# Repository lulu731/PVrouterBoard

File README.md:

# PVrouterBoard
PCB to manage PV power routing.

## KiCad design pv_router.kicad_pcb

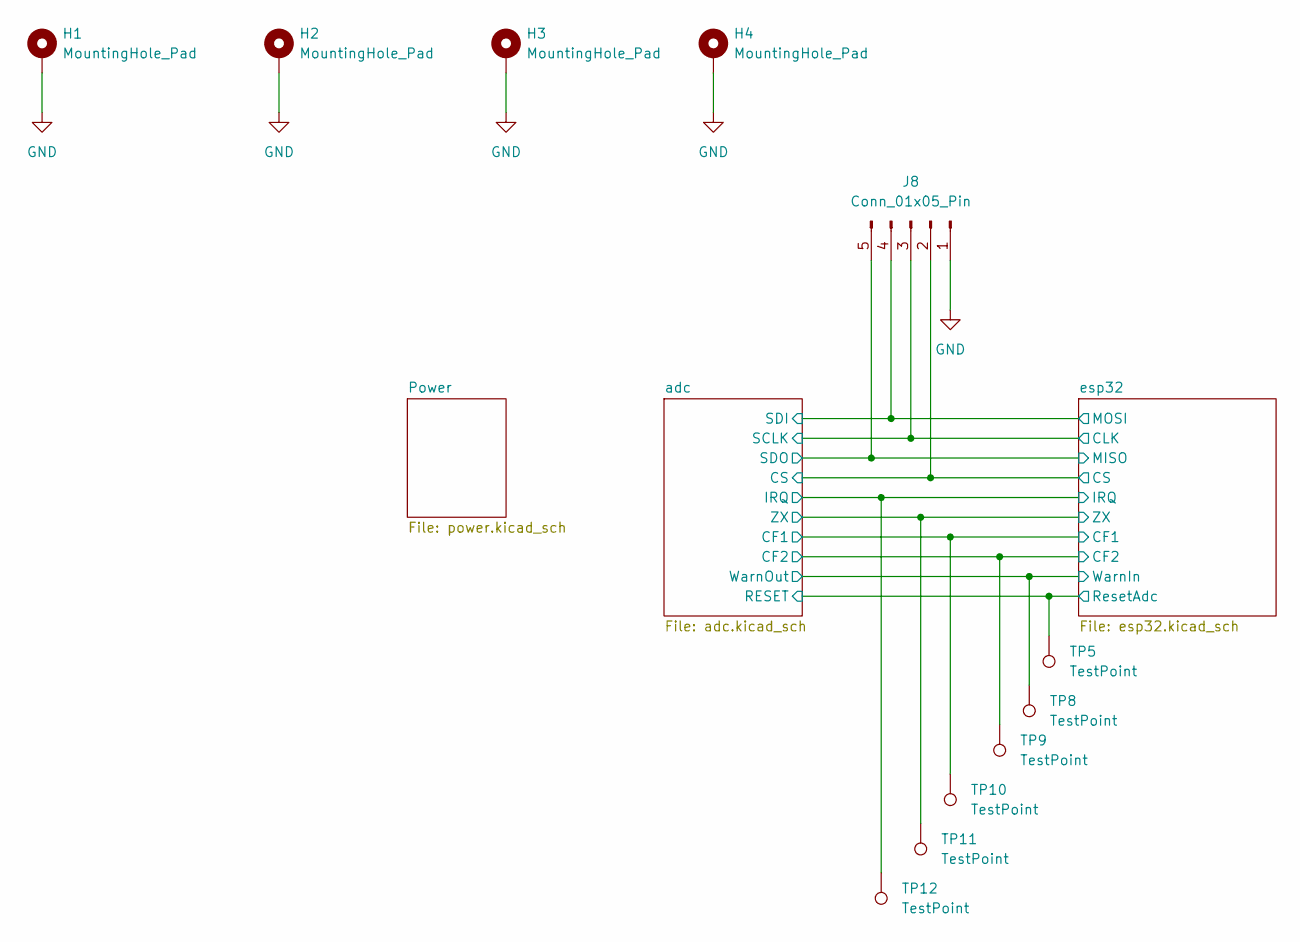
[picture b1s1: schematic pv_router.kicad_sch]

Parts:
H1, H2, H3, H4: MountingHole_Pad; MountingHole_2.7mm_Pad
J8: Conn_01x05_Pin; PinHeader_1x05_P2.54mm_Vertical
TP5, TP8, TP9, TP10, TP11, TP12: TestPoint; TestPoint_Pad_D1.0mm

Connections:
/adc/CF1: TP10.1; also elsewhere on the board
/adc/CF2: TP9.1; also elsewhere on the board
/adc/CS: J8.2; also elsewhere on the board
/adc/IRQ: TP12.1; also elsewhere on the board
/adc/RESET: TP5.1; also elsewhere on the board
/adc/SCLK: J8.3; also elsewhere on the board
/adc/SDI: J8.4; also elsewhere on the board
/adc/SDO: J8.5; also elsewhere on the board
/adc/WarnOut: TP8.1; also elsewhere on the board
/adc/ZX: TP11.1; also elsewhere on the board
GND: H1.1, H2.1, H3.1, H4.1, J8.1; also elsewhere on the board

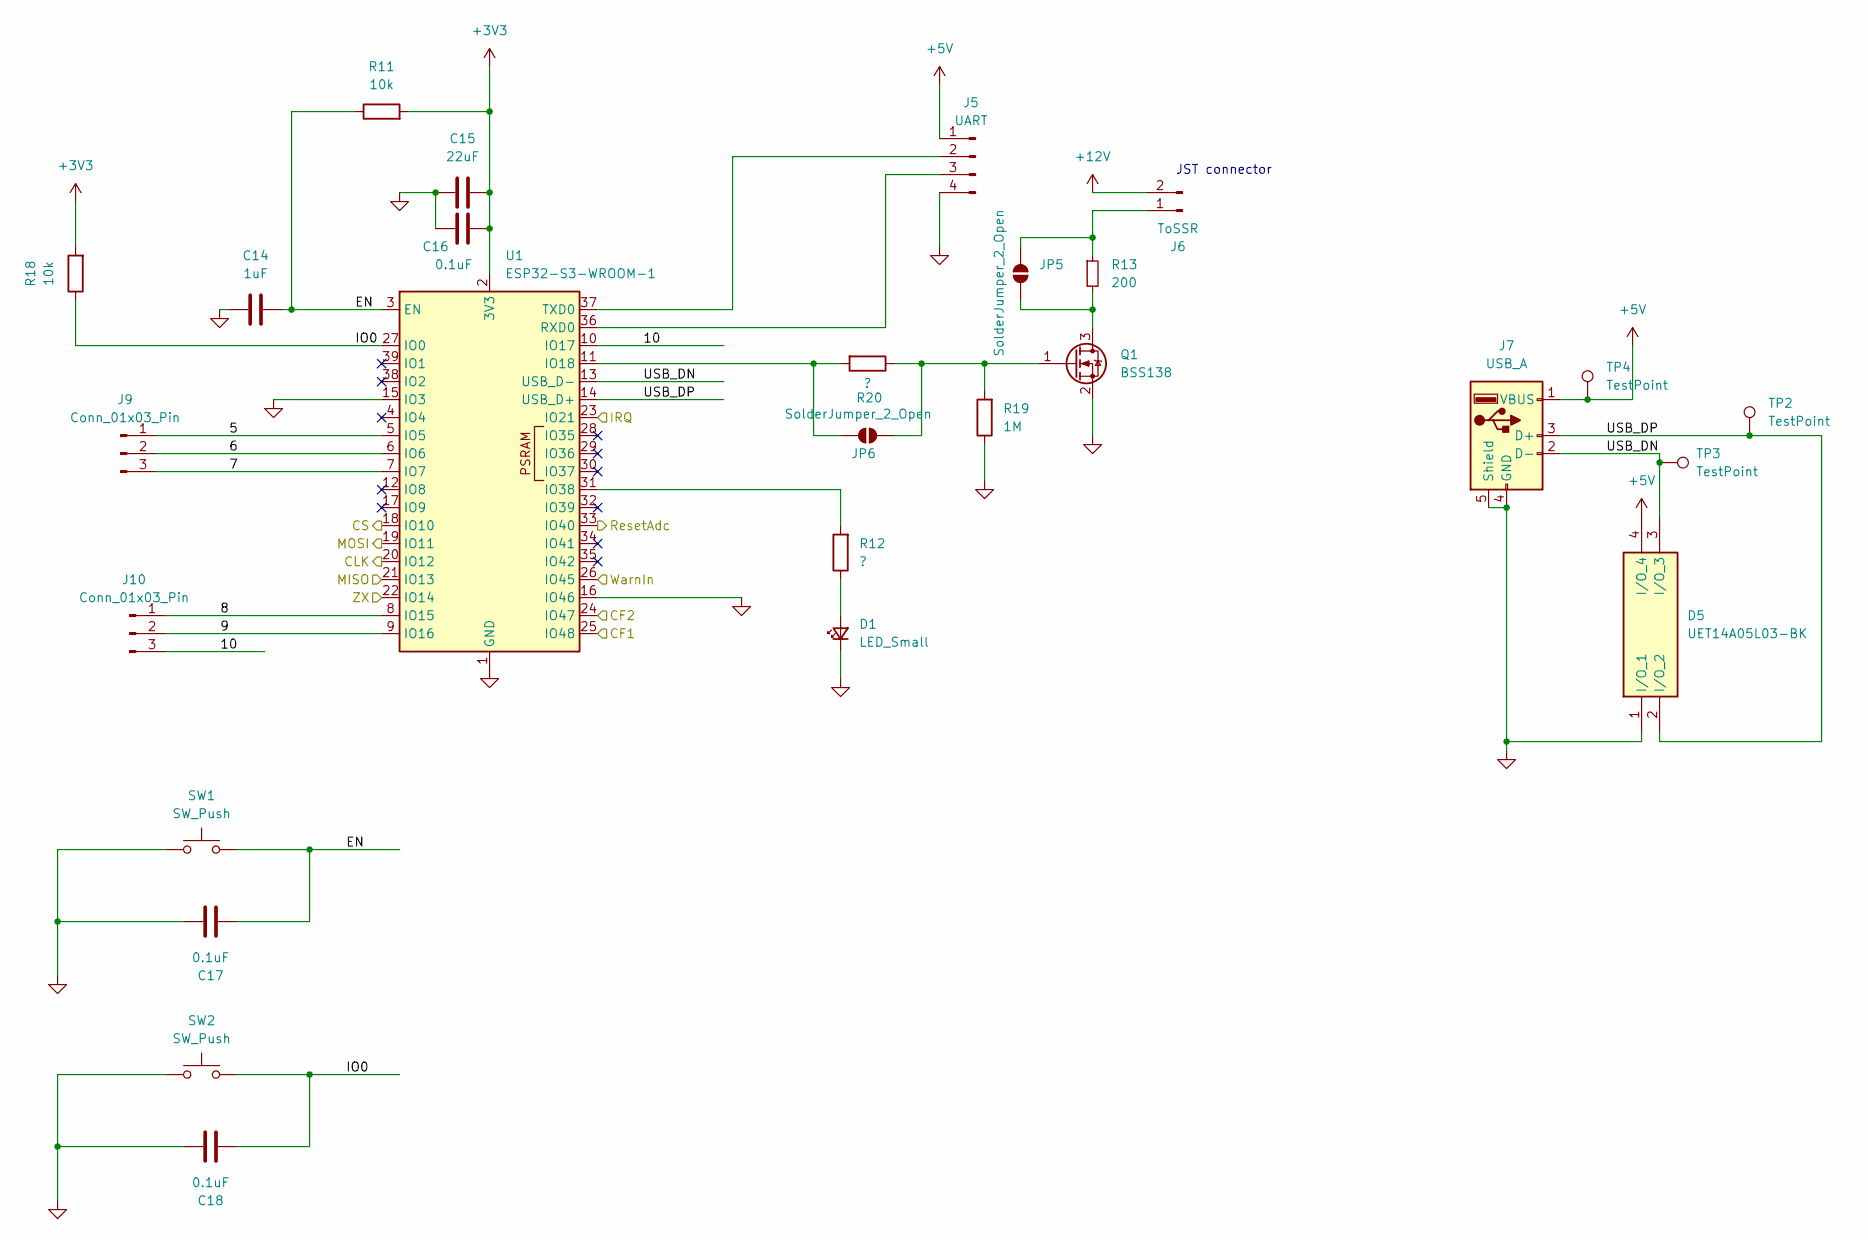
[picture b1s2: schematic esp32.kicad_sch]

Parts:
C14: 1uF; C_0805_2012Metric_Pad1.18x1.45mm_HandSolder
C15: 22uF; C_1210_3225Metric_Pad1.33x2.70mm_HandSolder
C16, C17, C18: 0.1uF; C_0805_2012Metric_Pad1.18x1.45mm_HandSolder
D1: LED_Small; LED_1206_3216Metric_Pad1.42x1.75mm_HandSolder
D5: UET14A05L03-BK; UET14A05L03BK; Mouser Part Number 603-UET14A05L03-BK
J5: UART; PinHeader_1x04_P2.54mm_Vertical
J6: ToSSR; JST_XH_S2B-XH-A_1x02_P2.50mm_Horizontal
J7: USB_A; USB-2.0-TYPE-A
J9, J10: Conn_01x03_Pin; PinHeader_1x03_P2.54mm_Vertical
JP5, JP6: SolderJumper_2_Open; SolderJumper-2_P1.3mm_Open_TrianglePad1.0x1.5mm
Q1: BSS138; SOT-23_Handsoldering
R11, R18: 10k; R_0805_2012Metric_Pad1.20x1.40mm_HandSolder
R12, R20: ?; R_Axial_DIN0207_L6.3mm_D2.5mm_P7.62mm_Horizontal
R13: 200; R_Axial_DIN0207_L6.3mm_D2.5mm_P7.62mm_Horizontal
R19: 1M; R_Axial_DIN0207_L6.3mm_D2.5mm_P7.62mm_Horizontal
SW1, SW2: SW_Push; SW_SPST_EVQQ2
TP2, TP3: TestPoint; TestPoint_THTPad_D1.5mm_Drill0.7mm
TP4: TestPoint; TestPoint_Pad_D2.0mm
U1: ESP32-S3-WROOM-1

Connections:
+3V3: C15.2, C16.2, R11.2, R18.2, U1.2 (3V3); also elsewhere on the board
+5V: D5.4 (I/O), J5.1, J7.1 (VBUS), TP4.1; also elsewhere on the board
+12V: J6.2; also elsewhere on the board
/adc/CF1: U1.25 (IO48); also elsewhere on the board
/adc/CF2: U1.24 (IO47); also elsewhere on the board
/adc/CS: U1.18 (IO10); also elsewhere on the board
/adc/IRQ: U1.23 (IO21); also elsewhere on the board
/adc/RESET: U1.33 (IO40); also elsewhere on the board
/adc/SCLK: U1.20 (IO12); also elsewhere on the board
/adc/SDI: U1.19 (IO11); also elsewhere on the board
/adc/SDO: U1.21 (IO13); also elsewhere on the board
/adc/WarnOut: U1.26 (IO45); also elsewhere on the board
/adc/ZX: U1.22 (IO14); also elsewhere on the board
/esp32/5: J9.1, U1.5 (IO5)
/esp32/6: J9.2, U1.6 (IO6)
/esp32/7: J9.3, U1.7 (IO7)
/esp32/8: J10.1, U1.8 (IO15)
/esp32/9: J10.2, U1.9 (IO16)
/esp32/10: J10.3, U1.10 (IO17)
/esp32/EN: C14.2, C17.2, R11.1, SW1.2, U1.3 (EN)
/esp32/IO0: C18.2, R18.1, SW2.2, U1.27 (IO0)
/esp32/USB_DN: D5.3 (I/O), J7.2 (D-), TP3.1, U1.13 (USB_D-)
/esp32/USB_DP: D5.2 (I/O), J7.3 (D+), TP2.1, U1.14 (USB_D+)
GND: C14.1, C15.1, C16.1, C17.1, C18.1, D1.1 (K), D5.1 (I/O), J5.4, J7.4 (GND), J7.5 (Shield), Q1.2 (S), R19.1, SW1.1, SW2.1, U1.1 (GND), U1.15 (IO3), U1.16 (IO46), U1.40 (GND), U1.41 (GND); also elsewhere on the board
unnamed: D1.2 (A), R12.1
unnamed: J5.2, U1.37 (TXD0)
unnamed: J5.3, U1.36 (RXD0)
unnamed: J6.1, JP5.2 (B), R13.1
unnamed: JP5.1 (A), Q1.3 (D), R13.2
unnamed: JP6.1 (A), R20.2, U1.11 (IO18)
unnamed: JP6.2 (B), Q1.1 (G), R19.2, R20.1
unnamed: R12.2, U1.31 (IO38)

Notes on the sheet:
JST connector

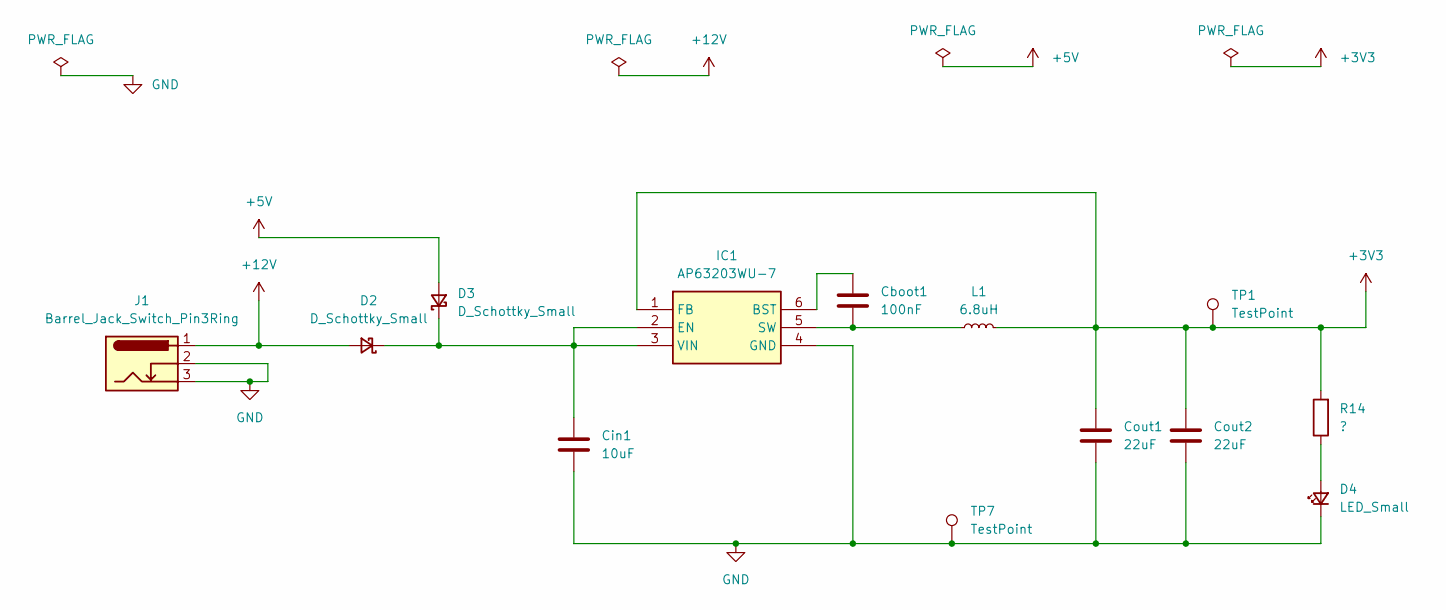
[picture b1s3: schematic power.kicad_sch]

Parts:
Cboot1: 100nF; C_0805_2012Metric_Pad1.18x1.45mm_HandSolder
Cin1: 10uF; C_0805_2012Metric_Pad1.18x1.45mm_HandSolder
Cout1, Cout2: 22uF; C_1210_3225Metric_Pad1.33x2.70mm_HandSolder
D2, D3: D_Schottky_Small; SODFL4724X90N
D4: LED_Small; LED_1206_3216Metric_Pad1.42x1.75mm_HandSolder
IC1: AP63203WU-7; AP63203WU7; Mouser Part Number 621-AP63203WU-7
J1: Barrel_Jack_Switch_Pin3Ring; BarrelJack_CUI_PJ-051A_Horizontal
L1: 6.8uH; L_Bourns_SRR1260
R14: ?; R_Axial_DIN0207_L6.3mm_D2.5mm_P7.62mm_Horizontal
TP1: TestPoint; TestPoint_Pad_D2.0mm
TP7: TestPoint; TestPoint_THTPad_D1.5mm_Drill0.7mm

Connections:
+3V3: Cout1.1, Cout2.1, IC1.1 (FB), L1.2, R14.2, TP1.1; also elsewhere on the board
+5V: D3.2 (A); also elsewhere on the board
+12V: D2.2 (A), J1.1; also elsewhere on the board
GND: Cin1.1, Cout1.2, Cout2.2, D4.1 (K), IC1.4 (GND), J1.2, J1.3, TP7.1; also elsewhere on the board
unnamed: Cin1.2, D2.1 (K), D3.1 (K), IC1.2 (EN), IC1.3 (VIN)
unnamed: D4.2 (A), R14.1
unnamed: Cboot1.2, IC1.6 (BST)
unnamed: Cboot1.1, IC1.5 (SW), L1.1

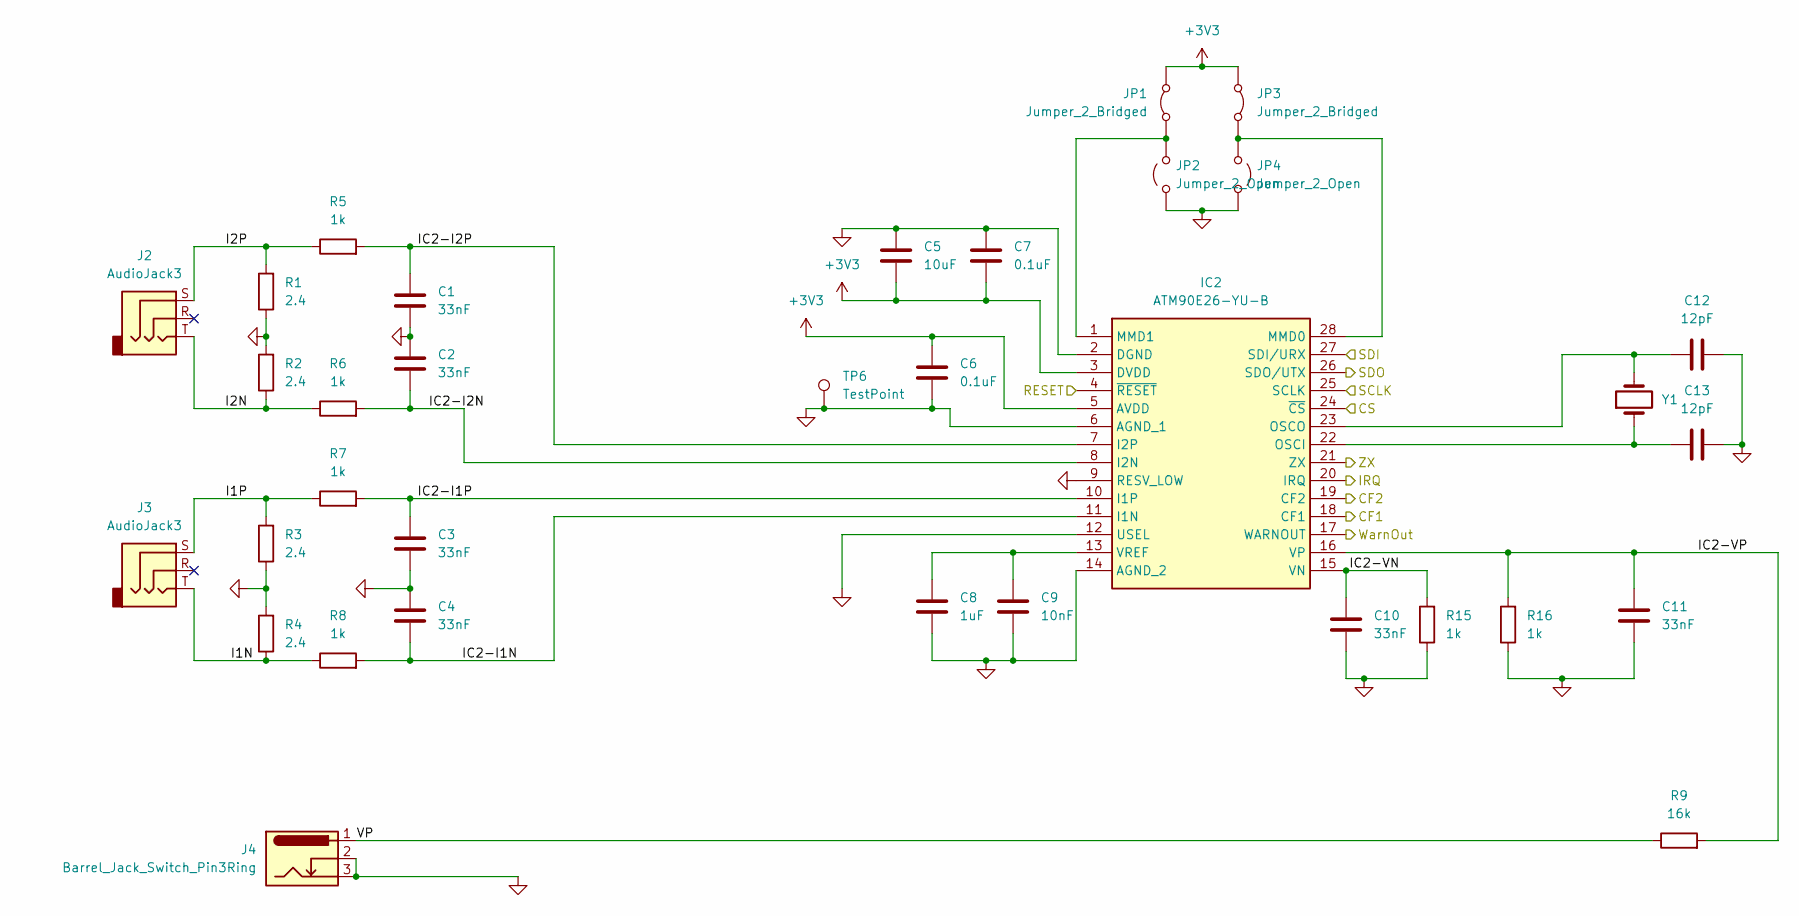
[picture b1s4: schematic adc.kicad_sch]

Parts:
C1, C2, C3, C4, C10, C11: 33nF; C_0805_2012Metric_Pad1.18x1.45mm_HandSolder
C5: 10uF; C_1210_3225Metric_Pad1.33x2.70mm_HandSolder
C6, C7: 0.1uF; C_0805_2012Metric_Pad1.18x1.45mm_HandSolder
C8: 1uF; C_0805_2012Metric_Pad1.18x1.45mm_HandSolder
C9: 10nF; C_0805_2012Metric_Pad1.18x1.45mm_HandSolder
C12, C13: 12pF; C_0805_2012Metric_Pad1.18x1.45mm_HandSolder
IC2: ATM90E26-YU-B; SOP65P778X199-28N; Mouser Part Number 556-ATM90E26-YU-B
J2, J3: AudioJack3; Jack_3.5mm_CUI_SJ1-3523N_Horizontal
J4: Barrel_Jack_Switch_Pin3Ring; BarrelJack_CUI_PJ-051A_Horizontal
JP1, JP3: Jumper_2_Bridged; TestPoint_2Pads_Pitch2.54mm_Drill0.8mm
JP2, JP4: Jumper_2_Open; TestPoint_2Pads_Pitch2.54mm_Drill0.8mm
R1, R2, R3, R4: 2.4; R_0805_2012Metric_Pad1.20x1.40mm_HandSolder
R5, R6, R7, R8, R15, R16: 1k; R_0805_2012Metric_Pad1.20x1.40mm_HandSolder
R9: 16k; R_0805_2012Metric_Pad1.20x1.40mm_HandSolder
TP6: TestPoint; TestPoint_THTPad_D1.5mm_Drill0.7mm
Y1: 8.192Mhz; HC_49US-_AT49__1

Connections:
+3V3: C5.2, C6.1, C7.2, IC2.3 (DVDD), IC2.5 (AVDD), JP1.2 (B), JP3.1 (A); also elsewhere on the board
/adc/CF1: IC2.18 (CF1); also elsewhere on the board
/adc/CF2: IC2.19 (CF2); also elsewhere on the board
/adc/CS: IC2.24 (~CS); also elsewhere on the board
/adc/I1N: J3.T, R4.1, R8.1
/adc/I1P: J3.S, R3.2, R7.1
/adc/I2N: J2.T, R2.1, R6.1
/adc/I2P: J2.S, R1.2, R5.1
/adc/IC2-I1N: C4.2, IC2.11 (I1N), R8.2
/adc/IC2-I1P: C3.1, IC2.10 (I1P), R7.2
/adc/IC2-I2N: C2.2, IC2.8 (I2N), R6.2
/adc/IC2-I2P: C1.1, IC2.7 (I2P), R5.2
/adc/IC2-VN: C10.1, IC2.15 (VN), R15.2
/adc/IC2-VP: C11.1, IC2.16 (VP), R9.2, R16.2
/adc/IRQ: IC2.20 (IRQ); also elsewhere on the board
/adc/RESET: IC2.4 (~RESET); also elsewhere on the board
/adc/SCLK: IC2.25 (SCLK); also elsewhere on the board
/adc/SDI: IC2.27 (SDI/URX); also elsewhere on the board
/adc/SDO: IC2.26 (SDO/UTX); also elsewhere on the board
/adc/VP: J4.1, R9.1
/adc/WarnOut: IC2.17 (WARNOUT); also elsewhere on the board
/adc/ZX: IC2.21 (ZX); also elsewhere on the board
GND: C1.2, C2.1, C3.2, C4.1, C5.1, C6.2, C7.1, C8.2, C9.2, C10.2, C11.2, C12.2, C13.2, IC2.2 (DGND), IC2.6 (AGND_1), IC2.9 (RESV_LOW), IC2.12 (USEL), IC2.14 (AGND_2), J4.2, J4.3, JP2.1 (A), JP4.2 (B), R1.1, R2.2, R3.1, R4.2, R15.1, R16.1, TP6.1; also elsewhere on the board
unnamed: IC2.28 (MMD0), JP3.2 (B), JP4.1 (A)
unnamed: IC2.1 (MMD1), JP1.1 (A), JP2.2 (B)
unnamed: C13.1, IC2.22 (OSCI), Y1.1
unnamed: C12.1, IC2.23 (OSCO), Y1.2
unnamed: C8.1, C9.1, IC2.13 (VREF)

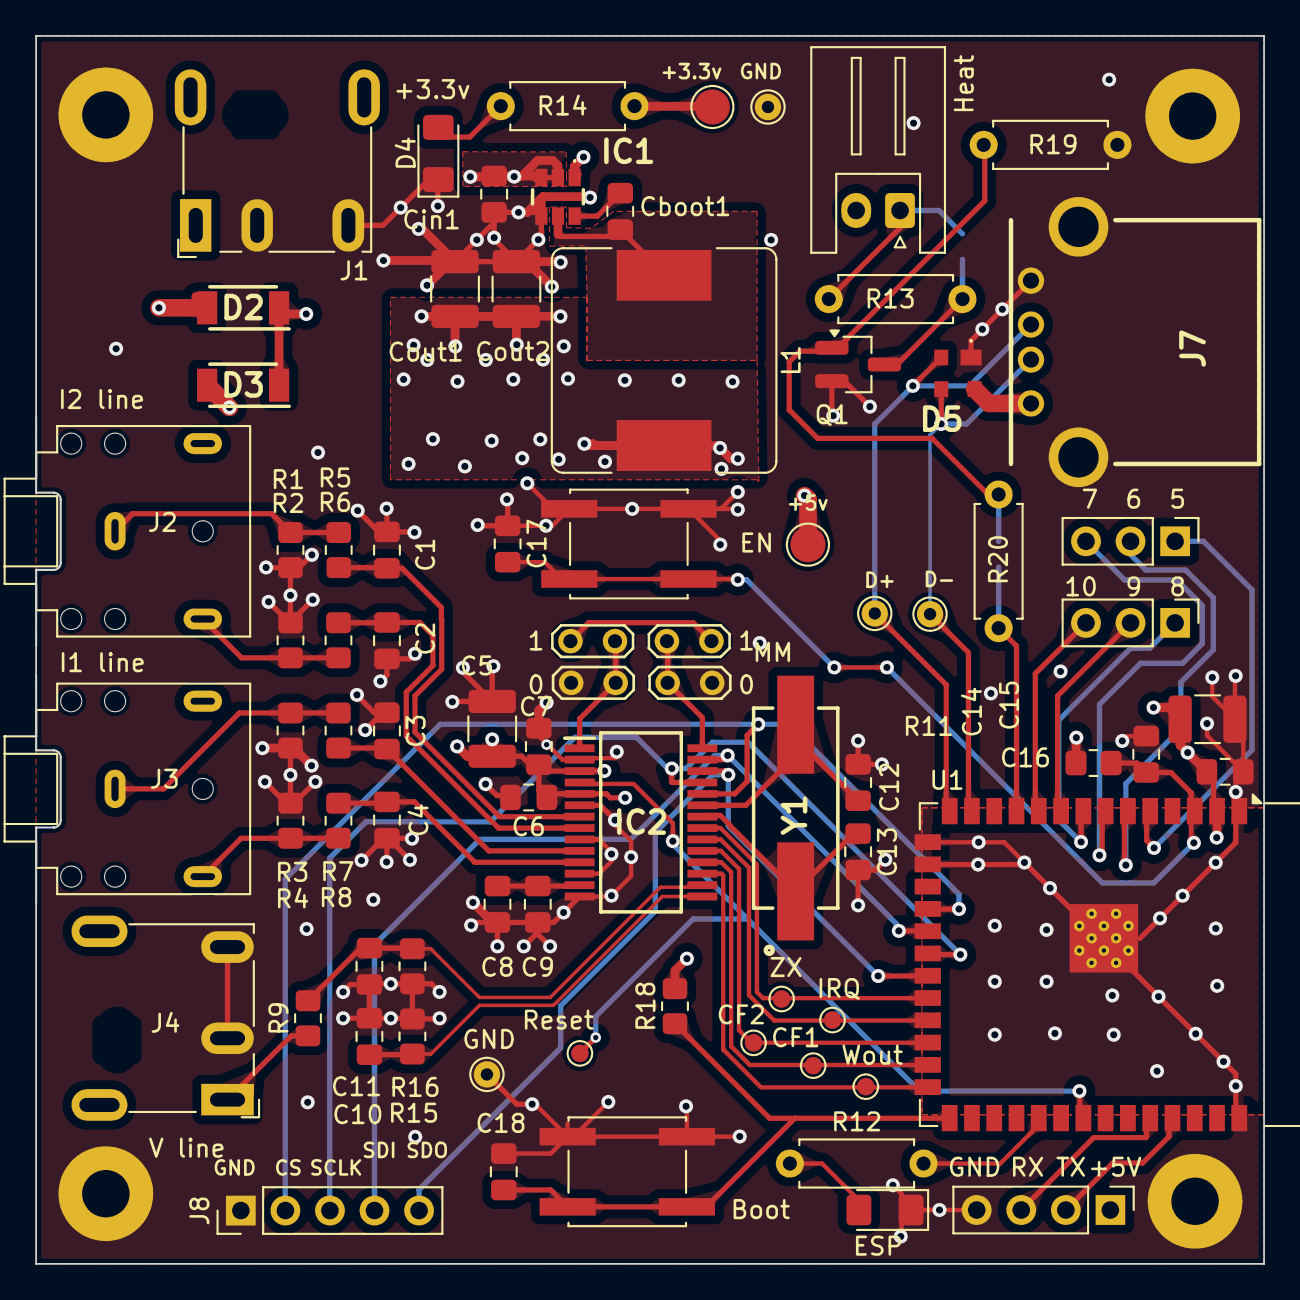
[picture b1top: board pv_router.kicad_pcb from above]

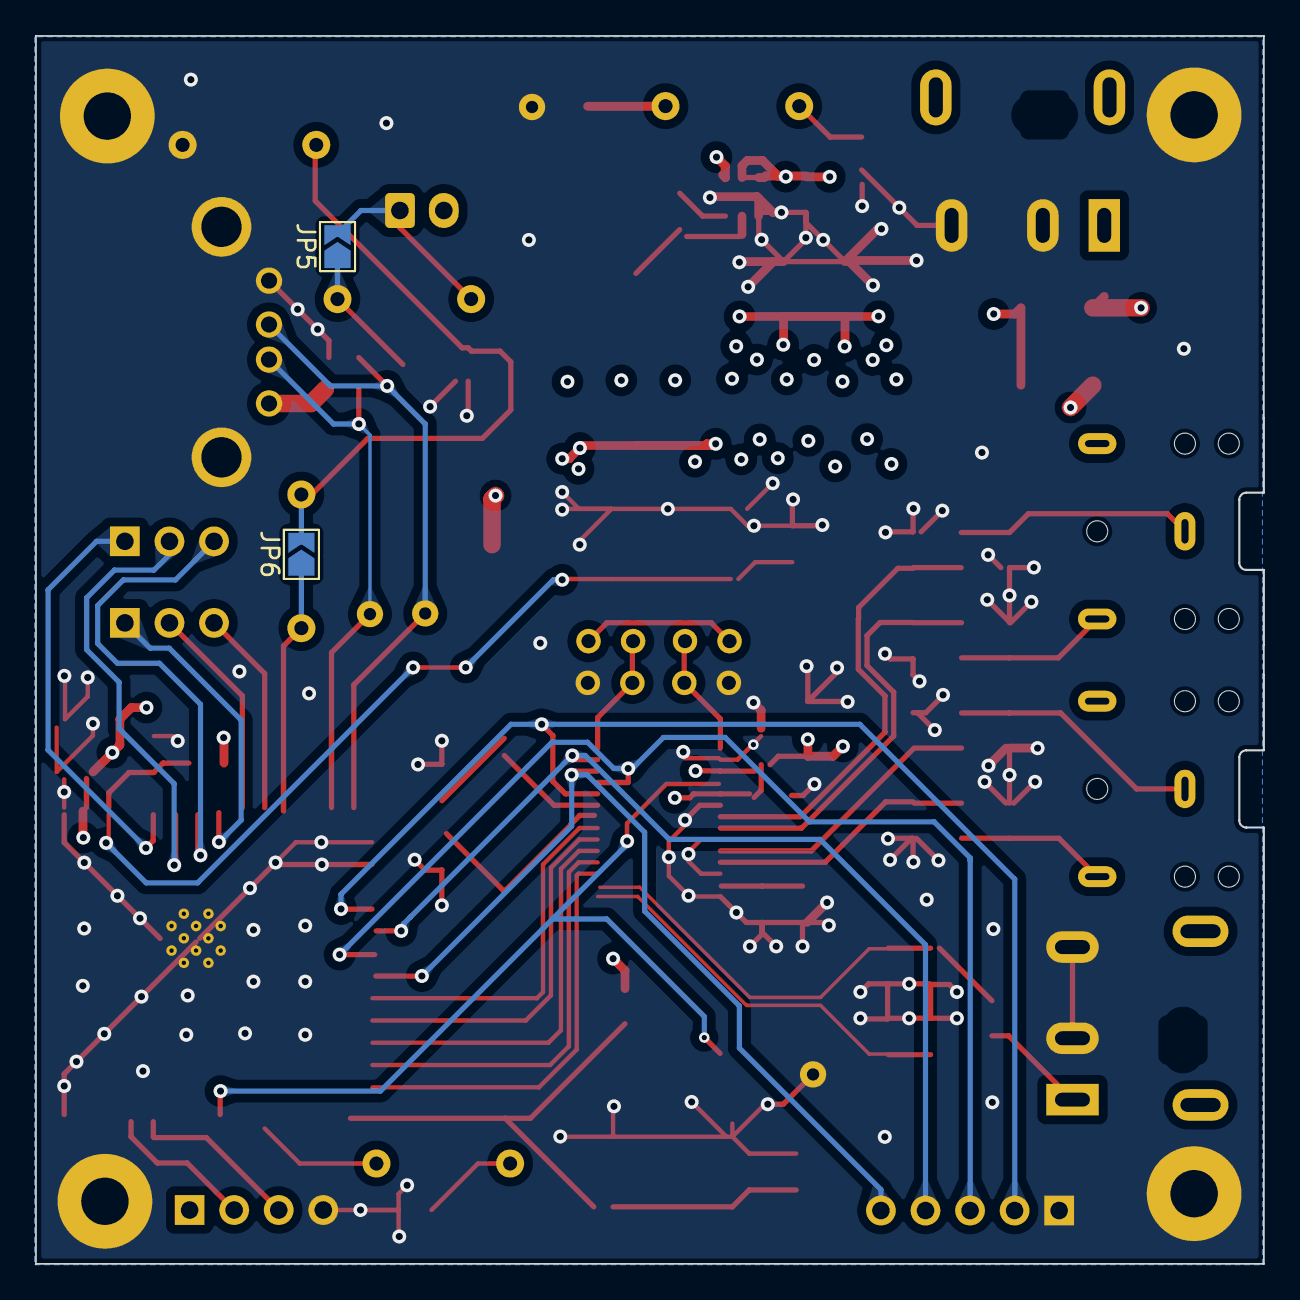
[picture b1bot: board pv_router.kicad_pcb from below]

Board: 4 copper layers, 70.0 x 70.0 mm, 85 parts (2 on the bottom side), 52 nets.

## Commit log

2023-12-12 ci: ignore .lck files and ignore/ dir
2023-12-12 feat: ADC + power 5V and USB
2024-01-04 lib: add ATM M90E26 AFE
2024-01-05 lib: add L6981 3.3V buck converter
2024-01-05 schem: update power sheet with L6981 3.3V buck converter
2024-01-06 feat: add adc component and associated sheet
2024-01-10 fix: anti-aliasing filters and adc grounding
2024-01-11 feat: add esp32 component
2024-01-12 ERC checked
2024-01-19 refactor: add burden resistor on CT lines
2024-01-22 PCB : add barrel jack FP
2024-01-22 fix: connections with sensors (CT and voltage)
2024-01-22 feat: add MOSFET to drive SSR
2024-01-22 check: ERC rules
2024-01-22 FP: assigned
2024-01-22 refactor: replace symbols
2024-01-22 fix: connect pin
2024-01-22 fix: init symbols references
2024-01-23 fix: assigned FP for ICs
2024-01-23 pcb: power module FPs set
2024-01-24 stagged
2024-01-25 fix: delete connection btw SDO and CLK net
2024-01-25 refactor: split 6 resistors network of low band filters in 2 + 4 networks
2024-01-25 pcb: first placement of FP, before routing
2024-01-28 pcb: first routing with freerouting
2024-01-28 ci: ignore *.kicad_pcb.zip files
2024-01-30 pcb: fix inductor value to 33uH
2024-01-30 FP: add inductor lib
2024-01-31 pcb: update stackup to aisler 2 layers simple param
2024-01-31 pcb: add aisler custom design rules
2024-02-01 PCB: define PWR equipot
2024-02-01 PCB: fix +3V3 track width to 0.6mm
2024-02-03 FP: first FP update
2024-02-03 FP: update 1k resistor array to smd FP
2024-02-03 FP: update SW1 FP
2024-02-03 FIX: update sizes of 1k resistor array
2024-02-03 fix: update FP
2024-02-05 FP: associate FP except jumpers
2024-02-07 PCB: first DCR
2024-02-08 PCB: adjust I1, I2, VP tracks length
2024-02-08 PCB: all tracks done
2024-02-12 PCB: set 4 layers PCB
2024-02-15 PCB: pour GND plane on In1 an B layers
2024-02-15 PCB: send 4th layer signal tracks to 3rd layer
2024-02-17 PCB: root 4 layers, resize board
2024-02-17 PCB: fix DRC errors
2024-02-17 PCB: fix some GND vias
2024-02-19 PCB: fix +3.3V track including zone
2024-02-19 PCB: fix GND tracks of ADC.
2024-02-20 PCB: adjust length tracks of pairs I1 and I2
2024-02-20 PCB: fix spaces between some tracks
2024-02-20 PCB: fix button GND track
2024-02-20 fix: schematic net names from board
2024-02-20 pcb: add mounting holes
2024-02-20 pcb: fix SPI tracks
2024-02-22 PCB: clean tracks and add teardrops
2024-02-22 fix: delete diode on input supply ic
2024-02-22 fix: J5 and J6 FP to 2.54mm headers
2024-02-22 fix: delete vias in pads
2024-02-22 PCB: add copper plane on layers 1 and 3
2024-02-22 PCB: add +3.3v copper zone
2024-02-22 feat: add LED on ESP32
2024-02-23 text: fix silkscreen errors and add connection ref
2024-02-27 fix: capacitor value
2024-02-27 pcb: define +3.3v planes in layers 1 and 3
2024-02-27 pcb: add GND vias in planes
2024-02-28 pcb: fix +3.3v plane
2024-02-29 pcb: add GND vias to some pads, layer 1
2024-02-29 fp: add barrel jack footprint in lib
2024-03-04 fix: barrel jack FP on PCB
2024-03-04 fix: BSS138 N-channel FET FP
2025-02-07 fix: split resistor network in 4 resistors
2025-02-10 FP: add AP63203 buck converter lib
2025-02-10 fix: use AP63203 buck conv
2025-02-11 fix: buck converter inductor value to 3.9uH
2025-02-13 fix: components numbers
2025-02-21 fp: fix some components prints
2025-02-21 fp: fix array 2 resistors print
2025-02-24 project: new Kicad 9 format
2025-02-25 fix: add schottky diode on main alim
2025-02-26 fix: move some component properties
2025-02-26 feat: add +5V power symbol for uart programming
2025-02-26 feat: add led at buck converter out pin
2025-03-03 fix: change 1k resistor array to 2 resistors
2025-03-07 fix: divider resistor value set to 16k
2025-03-09 fix: update esp32 strapping pad 2 to high level
2025-03-10 fix: add boot button for esp32
2025-03-17 lib: add ESP32-S3 lib
2025-03-17 feat: substitute esp32-c3 with esp32-s3
2025-03-18 lib: add ESD protection device for USB lines
2025-03-18 feat: add USB connector to ESP
2025-03-19 fix: add connector JST to SSR device
2025-03-19 fix: move libs in ignore/lib/ directory
2025-03-19 feat: add led lighting when SSR is on
2025-03-19 fix: use symbol lib path variable
2025-03-20 fix: symbols placement
2025-03-20 fix: after ERC check
2025-03-21 fix: add pull-up resistor to IO0 pin (boot mode)
2025-03-21 fp: update footprint lib
2025-03-25 lib: add crystal library
2025-03-25 fix: fix components footprints, resistors, crystal
2025-03-25 fix: clean tracks before new components placement
2025-03-27 fix: barrel jack component footprint
2025-03-27 ci: ignore bom directory
2025-03-27 fix: components placement before drawing tracks
2025-03-28 FP: add USB A and schotky FP
2025-03-28 fix: FP for USB connector and schotky diode
2025-03-29 fix: update SMD FP components to handsoldering
2025-03-29 fix: size of PCB - 70x70 - and clean tracks and vias
2025-03-29 fix: components placement
2025-03-29 fix: reconnect SSR FET to ESP32
2025-03-30 feat: add test points
2025-03-31 feat: tracking OK
2025-03-31 feat: add SPI bus test points
2025-03-31 fix: move USB connector, to place headers fm esp32
2025-03-31 feat: add two 3 pins headers connected to ESP32 free pins
2025-04-01 fix: update custom rule file
2025-04-02 fix: PCB DRC check
2025-04-02 fix: ESP 32 FP
2025-04-02 fix: add +3.3V zone on B.CU and GND zone under ESP 32
2025-04-03 fix: mounting hole to GND
2025-04-04 fix: components typo
2025-04-05 fix: delete SDI angle track
2025-04-05 fix: inner layer 1 GND zone
2025-04-06 fix: update PCB constraints and rules
2025-04-06 fix: stretch ESP GND thermal pad to 0.25mm
2025-04-07 fix: shorten GND pads to capacitors
2025-04-07 fix: silkscreen layer
2025-04-07 feat: add teardrops
2025-04-07 feat: add test points on ESP/CAN bus
2025-04-08 feat: add a power plane layer
2025-04-08 feat: add Power net class
2025-04-08 fix: route to power plane
2025-04-08 fix: mounting hole w/o pads
2025-04-08 fix: some vias size
2025-04-08 fix: GND poors on layers F, 2, B
2025-04-09 fix: set SMT LED to 1206 size
2025-04-09 fix: zones under buck converter
2025-04-09 fix: add +3.3V vias btw F layer and layer 3
2025-04-09 fix: reroute +12V track to enable direct +3.3V connections on buck converter pins
2025-04-09 fix: after DRC check
2025-04-09 fix: add some GND vias
2025-04-09 fix: DRC check
2025-04-10 fix: vias
2025-04-13 feat: add solder pins on back layer to SSR
2025-04-13 fix: GND zone location on back layer
2025-04-16 feat: add pulldown resistor and limiting resistor to gat MOSFET
2025-04-16 fix: delete SSR led, not useful
2025-04-16 fix: USB A FP, with 5 pads
